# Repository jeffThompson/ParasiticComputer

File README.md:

# ParasiticComputer

A computer that feeds off of human body heat, commissioned by Digital Spring Festival.

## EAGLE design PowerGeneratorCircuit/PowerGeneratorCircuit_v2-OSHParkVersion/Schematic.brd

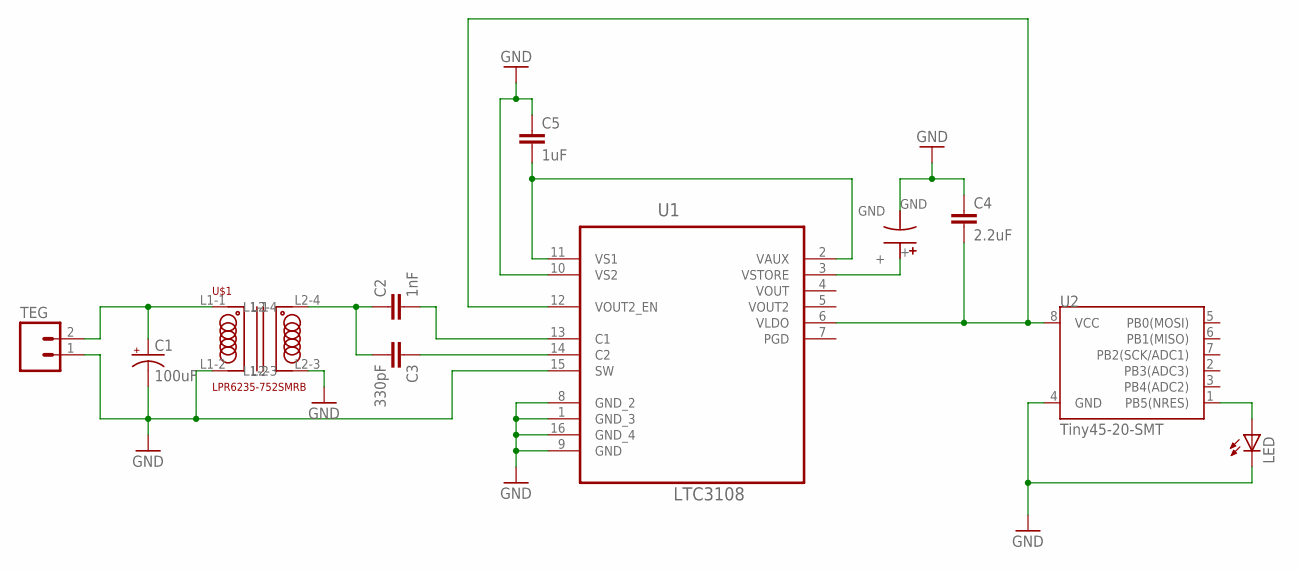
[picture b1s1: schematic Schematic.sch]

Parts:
C1: 100uF; EIA3216
C2: 1nF; 0603-CAP
C3: 330pF; 0603-CAP
C4: 2.2uF; 0603-CAP
C5: 1uF; 0603-CAP
C6: FC0V104FTBR24; FC0V104ZFTBR24
LED: LEDCHIPLED_0805; CHIPLED_0805
TEG: M02LOCK; 1X02_LOCK
U1: LTC3108; SOP63P600X175-16N
U2: Tiny45-20-SMT; SO08-EIAJ
U$1: LPR6235-752SMRB

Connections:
GND: C1.C (-), C4.1, C5.1, C6.GND, LED.C, TEG.1, U1.1 (GND_3), U1.8 (GND_2), U1.9 (GND), U1.10 (VS2), U1.15 (SW), U1.16 (GND_4), U2.4 (GND), U$1.L1-2, U$1.L2-3
unnamed: C2.1, C3.2, U$1.L2-4
unnamed: C5.2, U1.2 (VAUX), U1.11 (VS1)
unnamed: C2.2, U1.13 (C1)
unnamed: C3.1, U1.14 (C2)
unnamed: C6.+, U1.3 (VSTORE)
unnamed: C4.2, U1.6 (VLDO), U1.12 (VOUT2_EN), U2.8 (VCC)
unnamed: LED.A, U2.1 (PB5(NRES))
unnamed: C1.A (+), TEG.2, U$1.L1-1

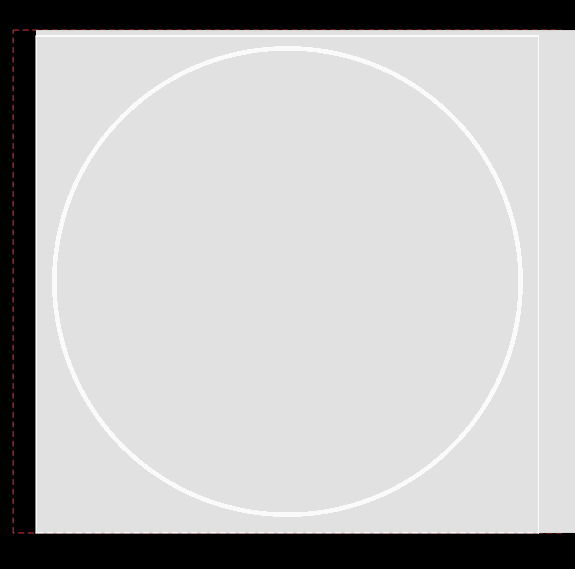
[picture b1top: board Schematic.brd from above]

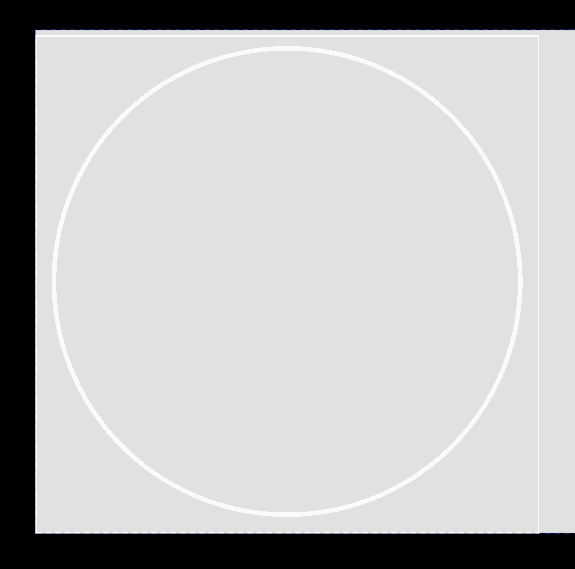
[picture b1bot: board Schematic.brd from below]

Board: 2 copper layers, 27.7 x 27.4 mm, 11 parts (5 on the bottom side), 9 nets.

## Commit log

2018-03-05 Cleanup unused firmware files
2018-03-05 Added documentation back in

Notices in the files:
parts and their libraries:
SparkFun-Capacitors: Licensing: Creative Commons ShareAlike 4.0 International - https://creativecommons.org/licenses/by-sa/4.0
